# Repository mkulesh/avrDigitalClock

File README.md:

#  "A digital clock based on ATmega644 MCU"

This repository provides hardware layout and firmware for a digital clock based on ATmega644 MCU

## Hardware design
This clock consist of two boards:
- the first display board contains four 0.8 inch. single digit numerical displays and one 2x16 chars LCD-display.

- the second board contains ATmega644 MCU with necessary periphery: voltage regulator, light sensor, temperature sensor, buttons, programming connector, 32.7680kHz crystal, DCF77 receiver with ferrite core.

PCB are developed in Eagle CAD (see directory pcb):

## Firmware
The firmware is written in C++ in Atmel Studio 6.0 (see directory src). The main idea here is to collect low-level routines in an object-oriented library and develop the main logic of the application using objects that implements different hardware elements.

## List of components
- DC connector: 1x DC-8N
- voltage regulators: 2x LD1117S33CTR
- temperature sensor: 1x LMT86LP
- voltage reference: 1x TL431CL3T
- 32.7680kHz crystal: 1x EuroQuartz PH32768X
- DCF77 receiver: 1x ELV Elektronik DCF-2 with ferrite core
- LED 3mm: 4x
- light sensor: 1v VT935G-B
- MCU ATMEGA644PA-AU TQFP-44
- transistors: 1xBC337-40, 1x J105
- piezo buzzer: 1x RMP-14SP
- buttons: 4x D6X
- shift register: 4x SN74HC595DR
- digital/analog converter: 1x MCP4901
- 7-segment display: 4x SC08-11SRWA
- LCD-display: 1x DOG-M162 with back-light (i.e EA LED55X31-R)

## There are some known problems in this project
- DCF-2 works really bad (instable signal): ether ferrite core or software problem
- Resting in Eagle design rules is invalid
- Wrong position of the DC connector: it shall be placed on bottom instaead of top of board
- voltage of 7-segment display and LCD back-light is regulated using MCP4901 and J105: regulation interal is too short

## License

This software is published under the *GNU General Public License, Version 3*

Copyright (C) 2014-2017 Mikhail Kulesh

This program is free software: you can redistribute it and/or modify it under the terms of the GNU General Public License as published by the Free Software Foundation, either version 3 of the License, or (at your option) any later version.

This program is distributed in the hope that it will be useful, but WITHOUT ANY WARRANTY; without even the implied warranty of MERCHANTABILITY or FITNESS FOR A PARTICULAR PURPOSE.  See the GNU General Public License for more details. You should have received a copy of the GNU General Public License along with this program.

If not, see [www.gnu.org/licenses](http://www.gnu.org/licenses).

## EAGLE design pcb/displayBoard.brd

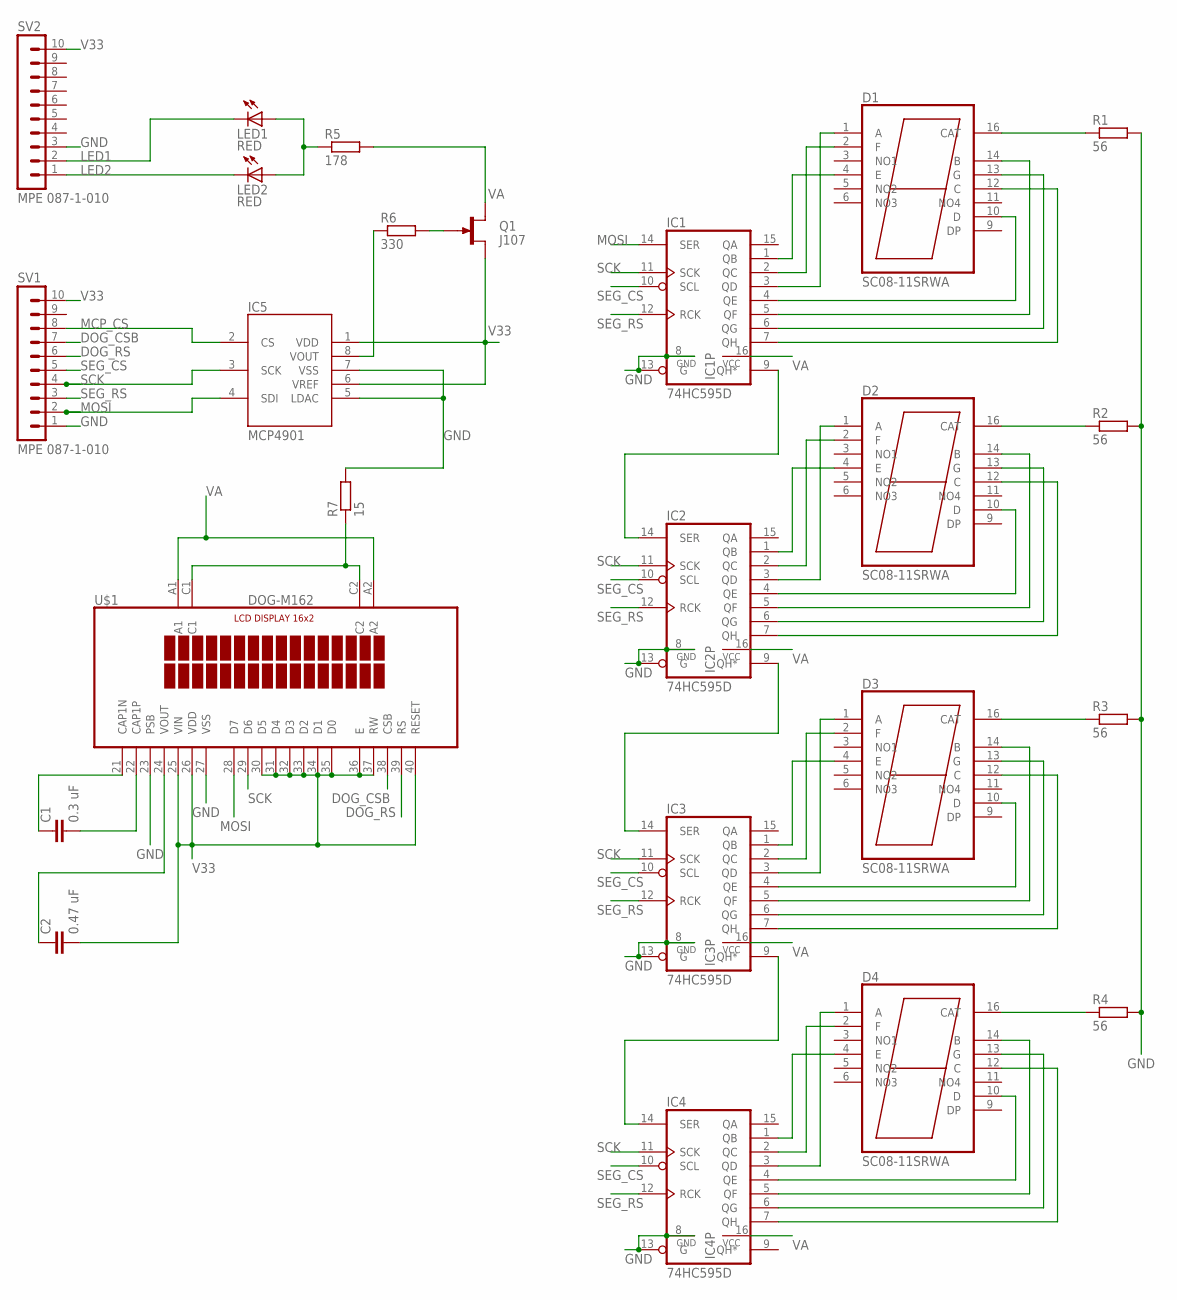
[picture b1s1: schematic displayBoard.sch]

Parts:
C1: 0.3 uF; C1206
C2: 0.47 uF; C1206
D1, D2, D3, D4: SC08-11SRWA
IC1, IC2, IC3, IC4: 74HC595D; SO16
IC5: MCP4901; MSOP8
LED1, LED2: RED; LED3MM
Q1: J107; TO92R
R1, R2, R3, R4: 56; R1206
R5: 178; R1206
R6: 330; R1206
R7: 15; R1206
SV1, SV2: MPE 087-1-010; MA10-1
U$1: DOG-M162; DOGM162

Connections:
DOG_CSB: SV1.7, U$1.38 (CSB)
DOG_RS: SV1.6, U$1.39 (RS)
GND: IC1.8 (GND), IC1.13 (G), IC2.8 (GND), IC2.13 (G), IC3.8 (GND), IC3.13 (G), IC4.8 (GND), IC4.13 (G), IC5.5 (LDAC), IC5.7 (VSS), R1.2, R2.2, R3.2, R4.2, R7.2, SV1.1, SV2.3, U$1.23 (PSB), U$1.27 (VSS)
LED1: LED1.K (C), SV2.2
LED2: LED2.K (C), SV2.1
MCP_CS: IC5.2 (CS), SV1.8
MOSI: IC1.14 (SER), IC5.4 (SDI), SV1.2, U$1.28 (D7)
unnamed: D1.4 (E), IC1.1 (QB)
unnamed: D1.2 (F), IC1.2 (QC)
unnamed: D1.1 (A), IC1.3 (QD)
unnamed: D1.10 (D), IC1.4 (QE)
unnamed: D1.14 (B), IC1.5 (QF)
unnamed: D1.13 (G), IC1.6 (QG)
unnamed: D1.12 (C), IC1.7 (QH)
unnamed: D2.4 (E), IC2.1 (QB)
unnamed: D2.2 (F), IC2.2 (QC)
unnamed: D2.1 (A), IC2.3 (QD)
unnamed: D2.10 (D), IC2.4 (QE)
unnamed: D2.14 (B), IC2.5 (QF)
unnamed: D2.13 (G), IC2.6 (QG)
unnamed: D2.12 (C), IC2.7 (QH)
unnamed: IC1.9 (QH*), IC2.14 (SER)
unnamed: D3.4 (E), IC3.1 (QB)
unnamed: D3.2 (F), IC3.2 (QC)
unnamed: D3.1 (A), IC3.3 (QD)
unnamed: D3.10 (D), IC3.4 (QE)
unnamed: D3.14 (B), IC3.5 (QF)
unnamed: D3.13 (G), IC3.6 (QG)
unnamed: D3.12 (C), IC3.7 (QH)
unnamed: D4.4 (E), IC4.1 (QB)
unnamed: D4.2 (F), IC4.2 (QC)
unnamed: D4.1 (A), IC4.3 (QD)
unnamed: D4.10 (D), IC4.4 (QE)
unnamed: D4.14 (B), IC4.5 (QF)
unnamed: D4.13 (G), IC4.6 (QG)
unnamed: D4.12 (C), IC4.7 (QH)
unnamed: IC3.9 (QH*), IC4.14 (SER)
unnamed: IC2.9 (QH*), IC3.14 (SER)
unnamed: D1.16 (CAT), R1.1
unnamed: D2.16 (CAT), R2.1
unnamed: D3.16 (CAT), R3.1
unnamed: D4.16 (CAT), R4.1
unnamed: LED1.A, LED2.A, R5.1
unnamed: C1.1, U$1.21 (CAP1N)
unnamed: C1.2, U$1.22 (CAP1P)
unnamed: C2.1, U$1.24 (VOUT)
unnamed: IC5.8 (VOUT), R6.1
unnamed: Q1.G, R6.2
unnamed: R7.1, U$1.C1, U$1.C2
SCK: IC1.11 (SCK), IC2.11 (SCK), IC3.11 (SCK), IC4.11 (SCK), IC5.3 (SCK), SV1.4, U$1.29 (D6)
SEG_CS: IC1.10 (SCL), IC2.10 (SCL), IC3.10 (SCL), IC4.10 (SCL), SV1.5
SEG_RS: IC1.12 (RCK), IC2.12 (RCK), IC3.12 (RCK), IC4.12 (RCK), SV1.3
V33: C2.2, IC5.1 (VDD), IC5.6 (VREF), Q1.S, SV1.10, SV2.10, U$1.25 (VIN), U$1.26 (VDD), U$1.30 (D5), U$1.31 (D4), U$1.32 (D3), U$1.33 (D2), U$1.34 (D1), U$1.35 (D0), U$1.36 (E), U$1.37 (RW), U$1.40 (RESET)
VA: IC1.16 (VCC), IC2.16 (VCC), IC3.16 (VCC), IC4.16 (VCC), Q1.D, R5.2, U$1.A1, U$1.A2

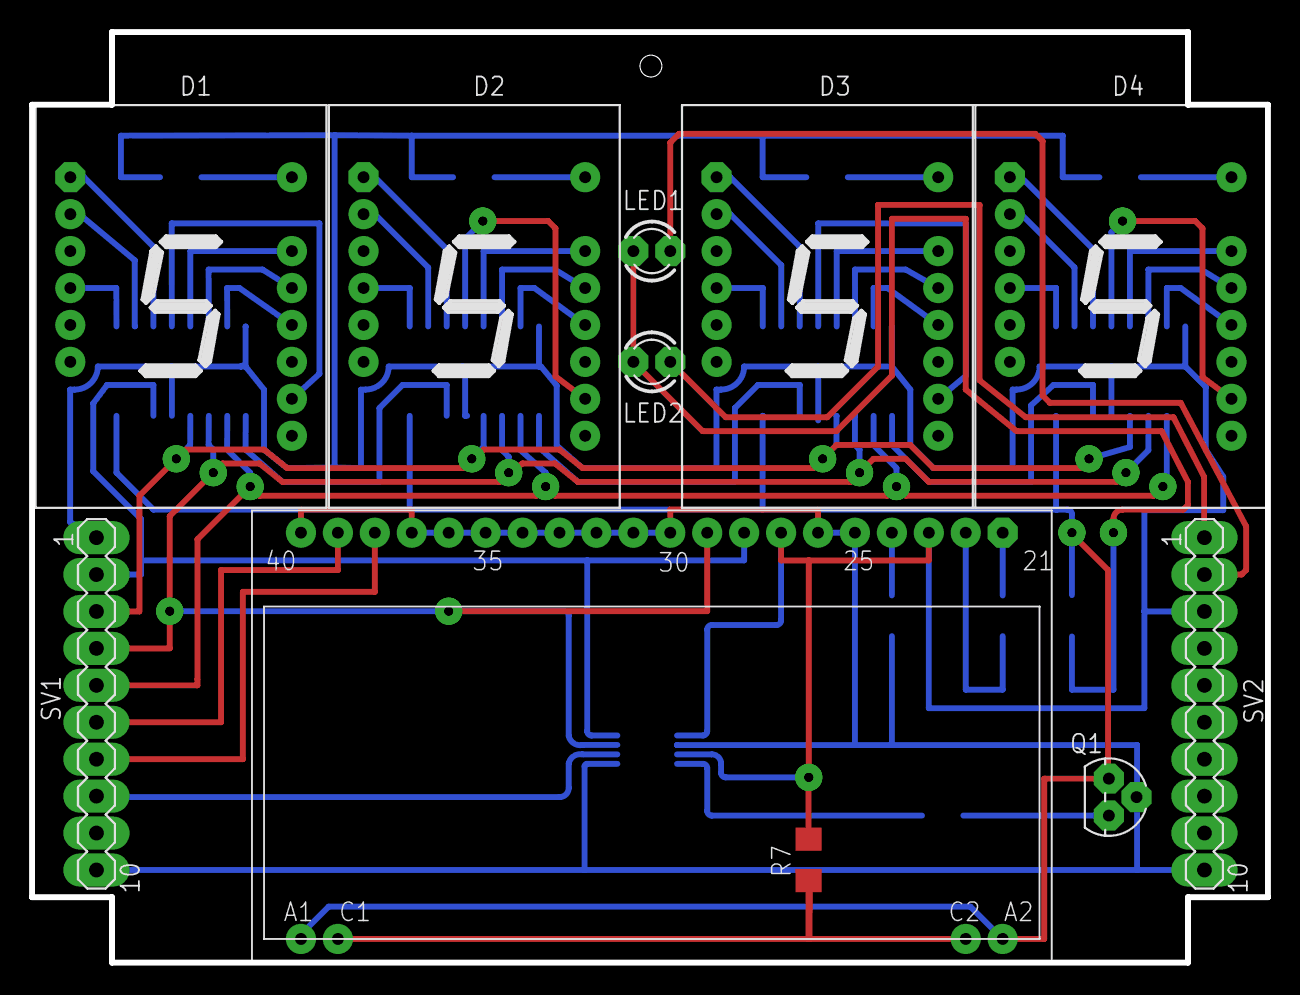
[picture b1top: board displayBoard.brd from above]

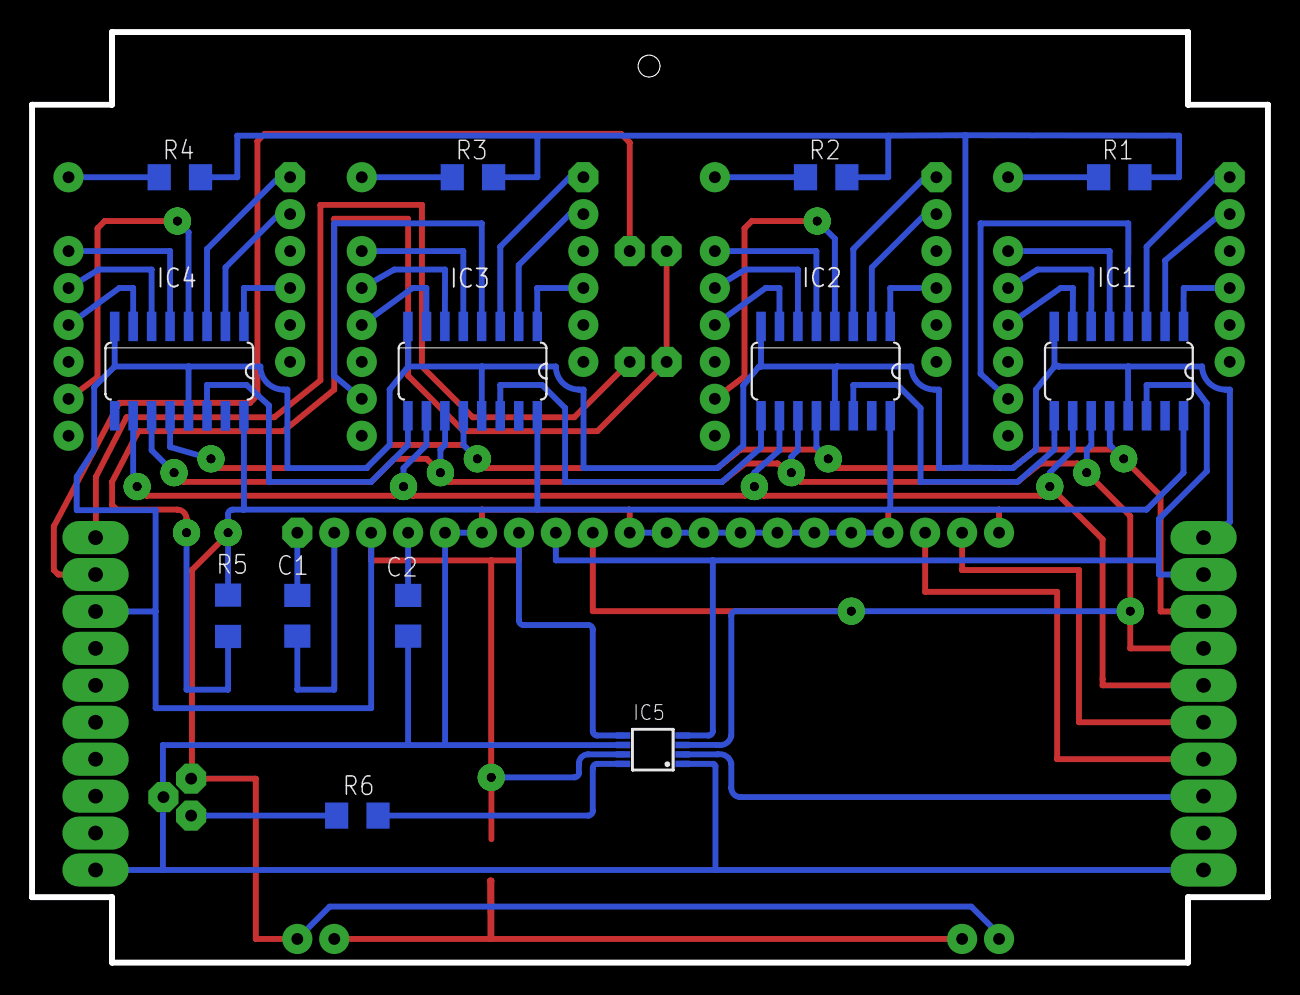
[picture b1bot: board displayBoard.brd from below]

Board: 2 copper layers, 85.0 x 64.0 mm, 24 parts (13 on the bottom side), 54 nets.

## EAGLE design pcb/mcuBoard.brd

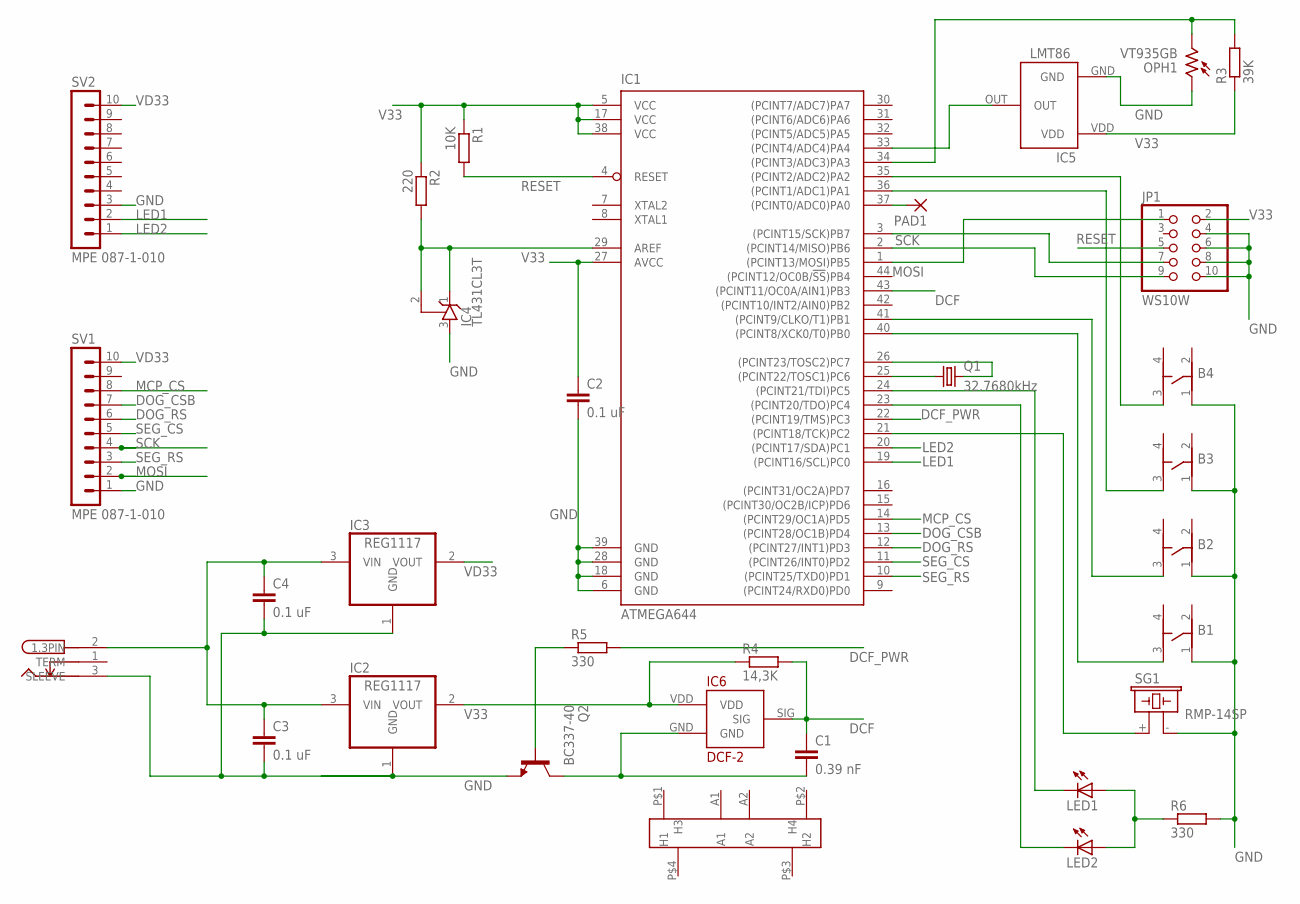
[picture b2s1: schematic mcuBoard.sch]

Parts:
B1, B2, B3, B4: BUTTON-D6X
C1: 0.39 nF; C1206
C2, C3, C4: 0.1 uF; C1206K
IC1: ATMEGA644; TQFP44
IC2, IC3: REG1117; SOT223
IC4: TL431CL3T; SOT23
IC5: LMT86
IC6: DCF77
JP1: WS10W; 2X05
LED1, LED2: LED3MM
OPH1: VT935GB; VT900
PAD1: 1,6/0,8
Q1: 32.7680kHz; MC-306
Q2: BC337-40; TO92
R1: 10K; M1206
R2: 220; M1206
R3: 39K; M1206
R4: 14,3K; R1206
R5: 330; R1206
R6: 330; M1206
SG1: RMP-14SP; F/CM12P
SV1, SV2: MPE 087-1-010; MA10-1
U$1: DC-8N; BUCHSE-1.3X3.75
U$2: DCF77-ANT

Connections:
DCF: C1.1, IC1.43 ((PCINT11/OC0A/AIN1)PB3), IC6.SIG, R4.2
DCF_PWR: IC1.22 ((PCINT19/TMS)PC3), R5.2
DOG_CSB: IC1.13 ((PCINT28/OC1B)PD4), SV1.7
DOG_RS: IC1.12 ((PCINT27/INT1)PD3), SV1.6
GND: B1.1, B2.1, B3.1, B4.1, C2.2, C3.2, C4.2, IC1.6 (GND), IC1.18 (GND), IC1.28 (GND), IC1.39 (GND), IC2.1 (GND), IC3.1 (GND), IC4.3 (A), IC5.GND, JP1.4, JP1.6, JP1.8, JP1.10, OPH1.1, Q2.1 (E), R6.2, SG1.- (2), SV1.1, SV2.3, U$1.3 (SLEEVE)
LED1: IC1.19 ((PCINT16/SCL)PC0), SV2.2
LED2: IC1.20 ((PCINT17/SDA)PC1), SV2.1
MCP_CS: IC1.14 ((PCINT29/OC1A)PD5), SV1.8
MOSI: IC1.1 ((PCINT13/MOSI)PB5), JP1.1, SV1.2
unnamed: C3.1, C4.1, IC2.3 (VIN), IC3.3 (VIN), U$1.2 (1.3PIN)
unnamed: IC1.2 ((PCINT14/MISO)PB6), JP1.9
unnamed: B3.3, IC1.36 ((PCINT1/ADC1)PA1)
unnamed: B2.3, IC1.41 ((PCINT9/CLKO/T1)PB1)
unnamed: B1.3, IC1.40 ((PCINT8/XCK0/T0)PB0)
unnamed: IC1.25 ((PCINT22/TOSC1)PC6), Q1.1
unnamed: IC1.29 (AREF), IC4.1 (C), IC4.2 (R), R2.2
unnamed: IC1.26 ((PCINT23/TOSC2)PC7), Q1.4 (2)
unnamed: IC1.21 ((PCINT18/TCK)PC2), SG1.+ (1)
unnamed: IC1.33 ((PCINT4/ADC4)PA4), IC5.OUT
unnamed: B4.3, IC1.35 ((PCINT2/ADC2)PA2)
unnamed: IC1.34 ((PCINT3/ADC3)PA3), OPH1.2, R3.2
unnamed: IC1.37 ((PCINT0/ADC0)PA0), PAD1.1
unnamed: C1.2, IC6.GND, Q2.3 (C)
unnamed: Q2.2 (B), R5.1
unnamed: LED1.A, LED2.A, R6.1
unnamed: IC1.24 ((PCINT21/TDI)PC5), LED1.K (C)
unnamed: IC1.23 ((PCINT20/TDO)PC4), LED2.K (C)
RESET: IC1.4 (RESET), JP1.5, R1.2
SCK: IC1.3 ((PCINT15/SCK)PB7), JP1.7, SV1.4
SEG_CS: IC1.11 ((PCINT26/INT0)PD2), SV1.5
SEG_RS: IC1.10 ((PCINT25/TXD0)PD1), SV1.3
V33: C2.1, IC1.5 (VCC), IC1.17 (VCC), IC1.27 (AVCC), IC1.38 (VCC), IC2.2 (VOUT), IC5.VDD, IC6.VDD, JP1.2, R1.1, R2.1, R3.1, R4.1
VD33: IC3.2 (VOUT), SV1.10, SV2.10

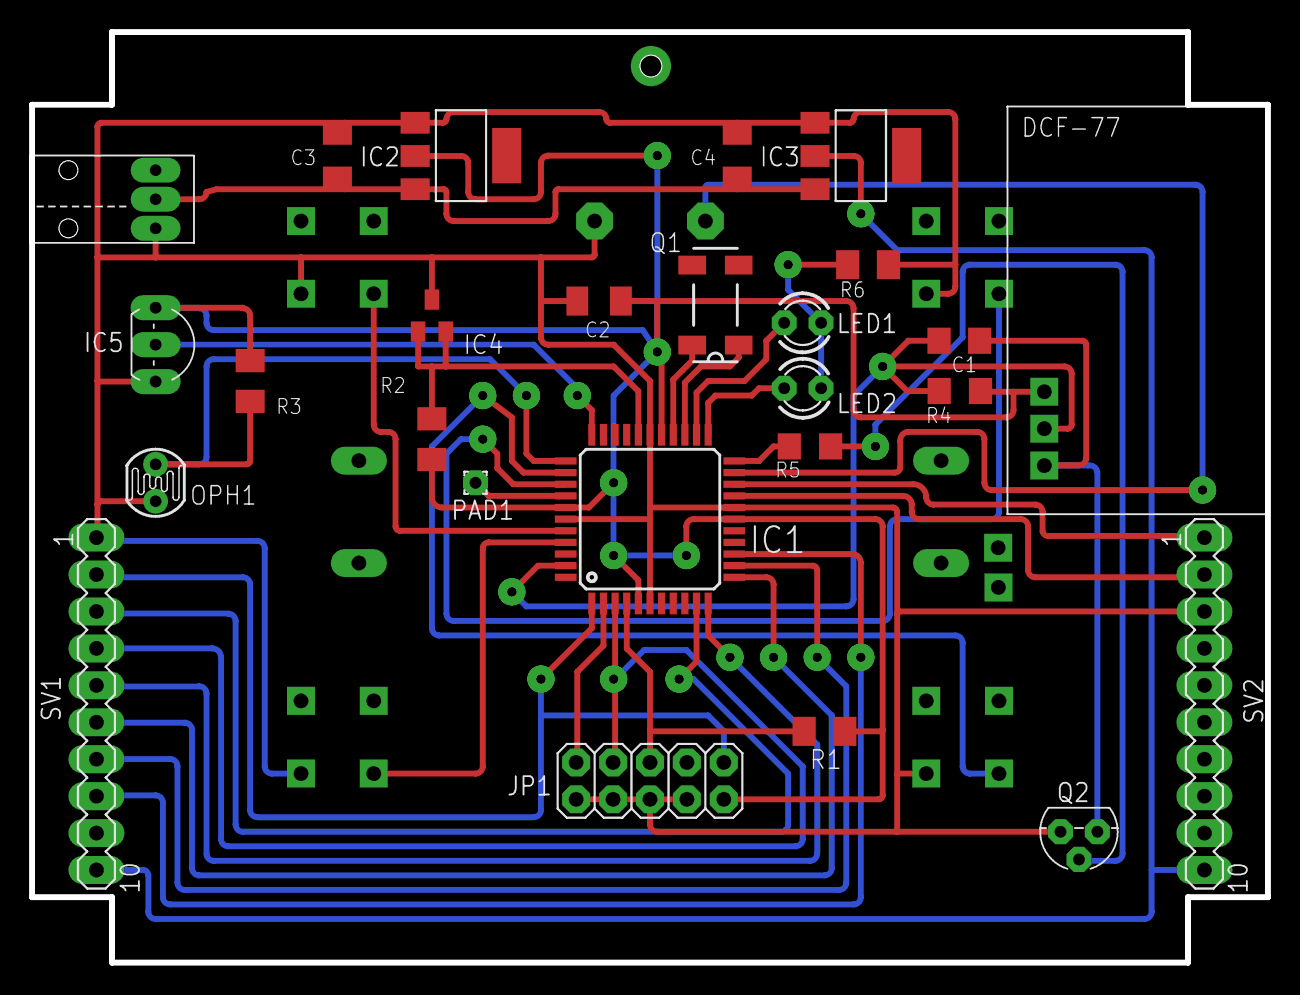
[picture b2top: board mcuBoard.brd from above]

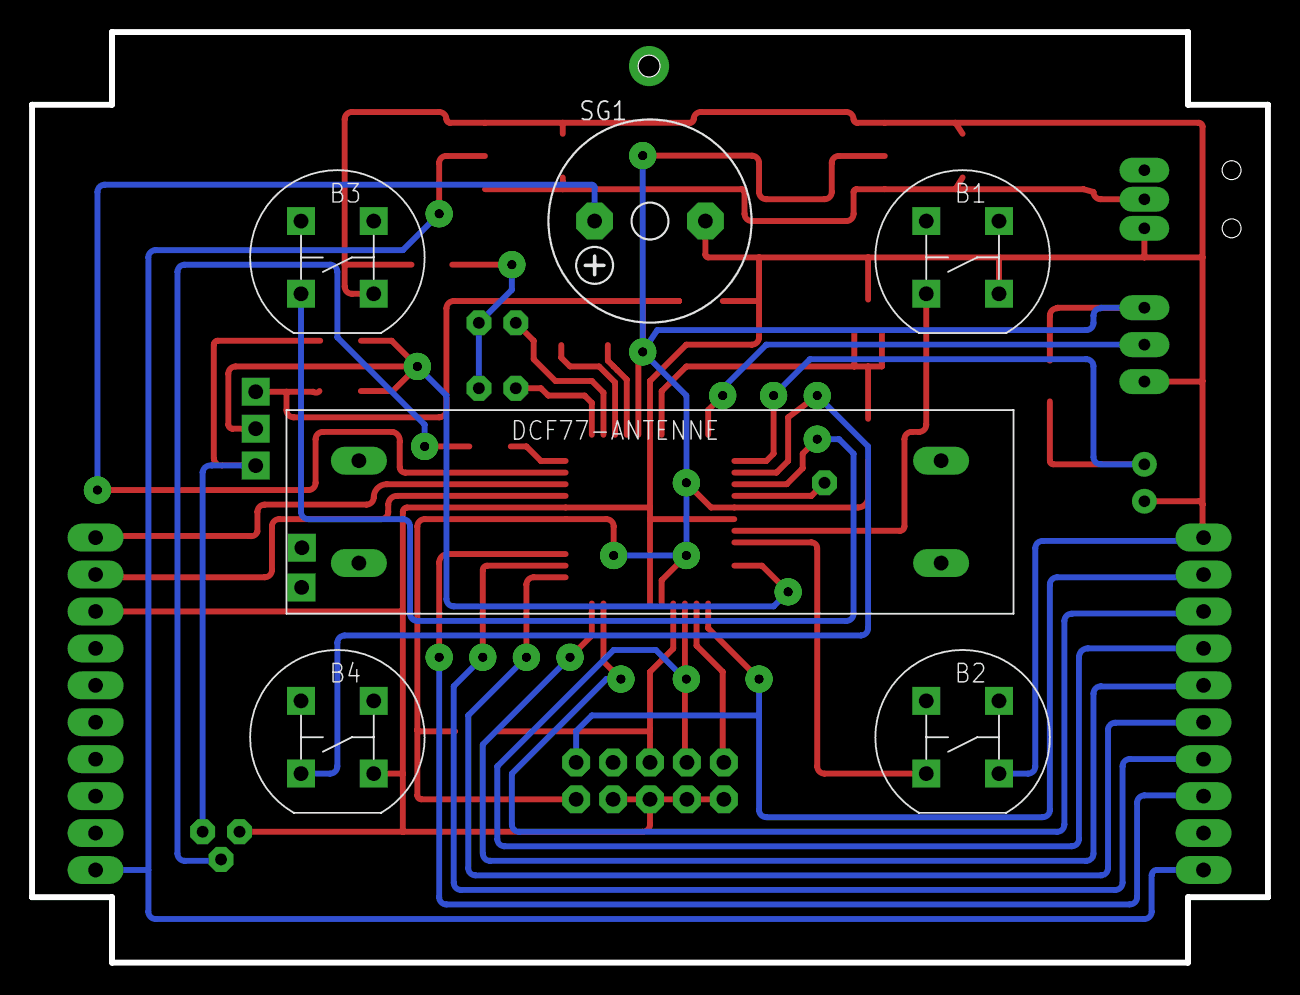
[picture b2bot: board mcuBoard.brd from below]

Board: 2 copper layers, 85.0 x 64.0 mm, 32 parts (6 on the bottom side), 33 nets.

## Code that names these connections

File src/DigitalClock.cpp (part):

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DigitalClock::DigitalClock(RealTimeClock * _rtc) :
        rtc(_rtc),
        mcuCS(IOPort::B, PB4, IOPort::OUTPUT),
        ledSec1(IOPort::C, PC0, Devices::Led::ANODE, true),
        ledSec2(IOPort::C, PC1, Devices::Led::ANODE, false),
        ssdLine(IOPort::D, PD2, Devices::Led::ANODE, false),
        ssd(IOPort::B, PB5, PB7, IOPort::D, PD1), 
        displayBrightness(IOPort::B, PB5, PB7, IOPort::D, PD5),
        lcd(IOPort::B, PB5, PB7, IOPort::D, PD4, PD3),
        bMode(IOPort::B, PB0, _rtc),
        bActiveElement(IOPort::B, PB1, _rtc),
        bPlus(IOPort::A, PA1, _rtc),
        bMinus(IOPort::A, PA2, _rtc),
        piezoAlarm(IOPort::C, PC2, _rtc),
        ledToggle(_rtc, 500, 1),
        secToggle(_rtc, 1000),
        activeElementToggle(_rtc, 250, 3),
        returnToHome(_rtc, 30000, 1),
        secondsCorrection(_rtc, 4870000L, 1),
        adc(),
        dcfSignal(rtc, IOPort::B, PB2, IOPort::B, PB3),
        dcfBitReceived(IOPort::C, PC5, Devices::Led::ANODE, false),
        dcfBitFailed(IOPort::C, PC4, Devices::Led::ANODE, false),
        dcfPower(IOPort::C, PC3, Devices::Led::ANODE, false),
        dcfData(),
        activeElementVisible(false),
        homeScreen(),
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
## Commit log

2017-08-19 Updated images
2017-08-19 Source code formatted
2023-07-21 Added description

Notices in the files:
README.md:
License: GNU GPLv3
